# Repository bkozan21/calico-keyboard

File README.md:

# Calico Split Keyboard

This repository contains software and CAD files for a custom wireless split keyboard. I uses ZMK as firmware. The rest of this README is a tutorial about how to make this or a similar keyboard.

# Final product in action

[0001-1000.mp4](Split%20Keyboard/0001-1000.mp4)

# Table of contents

# Introduction

This was a personal project idea. I spent a lot of time during a week in front of a computer typing. Modern keyboards are not that ergonomic. As I was looking for a better keyboard, I came across custom keyboards and decided to make my own.

## Inspiration and Useful Sources

### Main Inspiration

These two videos from Ben Vallack and Christian Selig were my main inspiration. During the design and making of my own keyboard, I went back to these videos quite frequently. If you need more information about something, start with these videos.

[“The REAL Ergonomic Keyboard Endgame!” - How To Design & Make A Totally Custom Keyboard](https://www.youtube.com/watch?v=UKfeJrRIcxw)

[I Built My Dream Keyboard from Absolute Scratch](https://www.youtube.com/watch?v=7UXsD7nSfDY)

Here are the GitHub repositories for the keyboards from the videos above:

[ergogen/input/config-flipper.yaml at master · benvallack/ergogen](https://github.com/benvallack/ergogen/blob/master/input/config-flipper.yaml)

[caldera-keyboard/ergogen/config.yaml at main · christianselig/caldera-keyboard](https://github.com/christianselig/caldera-keyboard/blob/main/ergogen/config.yaml)

### Other useful sources and inspirations

https://www.frandieguez.com/posts/how-to-build-a-split-keyboard-lily58-pro/#putting-all-together

https://github.com/makgyber/kiai-split

https://www.ubiqueiot.com/posts/xiao-nrf52840-zmk

https://github.com/ubiqueIoT/GigaPad/tree/main

This is a very good and detailed tutorial for the ergogen software I used:

[Let's Design A Keyboard With Ergogen v4: Introduction](https://flatfootfox.com/ergogen-introduction/)

[Let's Design A Keyboard With Ergogen v4: Reversible Split Keyboard Tips](https://flatfootfox.com/ergogen-part6-reversible-split/)

# Ingredients

<aside>
ℹ️

You don’t have to buy the items from the links I added. You can use any supplier or store or an equivalent product as long as it is compatible.

</aside>

| Name | Link | Quantity | Notes |
| --- | --- | --- | --- |
| Kailh Low Profile Choc Switches | https://splitkb.com/products/kailh-low-profile-choc-switches?variant=32171144380493&_su_rec=K7XPEFOSKQJ6HuOqu8JvlqgQJot6nW1wtNrVSzVyanA3C1YqsAHD4RuTCrJwP6FZxHm1uhMl3X4t7QNzuMuESyQ1RrEEgi36AF2GOhwYCAo9edE3fmjca5diy_bAAWXqCz8KgsL9PHYvucSHRDPHljyZl6D8sljBpnwmTNCeQKEJPHhKLW_XfV4Vj7vQilxc3kevMZ2U6zh7X3NKLHTFHpHWZRXFbdY0bCzeEJDRBogsHo5YQ6zEQlgKb0bRMkyONT2hpbjF&_su_rec_id=4e69f0e8-41da-4f02-ba84-3d4b565eb13f-1793966067 | 108 | I used 10 brown switches. Those are the arrow keys on both sides. For the red, I used reds. I did this because I was curious of the feeling of the browns. You can mix and match like me or stick to one type. |
| Keycap set | https://splitkb.com/products/mbk-legend-40s-choc-low-profile-keycaps?variant=43111026753795 | 1 | It doesn’t come with enough keycaps for a 108 key keyboard. You need extra keycaps if you have lots of keys. |
| Blank keycaps | https://splitkb.com/products/blank-mbk-choc-low-profile-keycaps?variant=31811487039565 | 56 | It might be a good idea to buy a couple more than you need just in case. Also, in the link I pasted, there are multiple options. I got only “10 x 1u”. That is a pack with ten 1 unit keycaps. |
| Kailh Hotswap Sockets | https://splitkb.com/products/kailh-hotswap-sockets?variant=39472161456205 | 108 | Make sure that you get the “choc” version. They need to match the switches. |
| SMD Diodes | https://splitkb.com/products/smd-diodes?variant=42283984060675 | 108 |  |
| nice!nano Microcontroller board | https://splitkb.com/products/nice-nano?variant=39408154116173 | 2 |  |
| Mill Max Low Profile Sockets | https://splitkb.com/products/mill-max-low-profile-sockets?variant=31945995845709 | 2 | I didn’t like these sockets that much. It is nice that they place the MCU board low but the pins are very thin. It is easy to bend a pin. You can also use a normal male and female headers. |
| JST PH 2 pin Female Socket | https://www.digikey.nl/en/products/detail/jst-sales-america-inc/S2B-PH-K-S/926626 | 2 |  |
| Li-Po battery | https://www.tinytronics.nl/en/power/batteries/li-po/pkcell-li-po-battery-3.7v-150mah-jst-ph-lp402025https://www.tinytronics.nl/en/power/batteries/li-po/pkcell-li-po-battery-3.7v-150mah-jst-ph-lp402025 | 2 | You can use a different capacity one. |
| Small on/off switch | https://www.tinytronics.nl/en/switches/manual-switches/slide-switches/small-switch-for-pcb-or-breadboard | 2 |  |
| Small pushbutton | https://www.tinytronics.nl/en/switches/manual-switches/pcb-switches/tactile-pushbutton-switch-momentary-4pin-6*6*6mm | 2 |  |
| M3 spacer - 10 mm - female to female |  | 22 |  |
| M3 bolt - 10 mm | https://www.tinytronics.nl/en/tools-and-mounting/installation-and-mounting-material/bolts/m3-bolt-10mm-thread-100-pieces | 22 |  |
| M3 bolt - 5 mm | https://www.tinytronics.nl/en/tools-and-mounting/installation-and-mounting-material/bolts/m3-bolt-5mm-thread-100-bolts | 22 |  |
| Rubber feet | https://nl.bauhaus/vilt-meubeldoppen/fix-o-moll-antislip-en-geluiddempers-12-mm/p/20893129 | At least 8 | I used 4 per side but in the 3d models, I added places for more. |

<aside>
⚠️

Be very careful with the LiPo battery. Do not puncture or cut it. Do not short its cables. Otherwise, it might explode and/or cause a fire.

</aside>

<aside>
ℹ️

I call my keyboard “Calico”. (It comes from the cat fur pattern). I don’t exactly know why I chose this name. 

</aside>

<aside>
ℹ️

All the software, 3d files, and the PCB files are on a GitHub repository. You can just use those files if you are making the exact same keyboard or use them as inspiration.

[GitHub - bkozan21/calico-keyboard](https://github.com/bkozan21/calico-keyboard/)

</aside>

# Making the layout (Ergogen)

<aside>
ℹ️

My goal for using ergogen was to generate a PCB layout. If you want to design your own layout, keep reading this section. If you are replicating my design, you can just get the PCB from my GitHub repository and skip to the next section.

https://github.com/bkozan21/calico-keyboard

</aside>

I used a software called ergogen to create the layout of my keyboard. It is a software for creating custom keyboard layouts. It can generate dxf files that you can use for designing a case and more importantly it can automatically generate a KiCad pcb file with the footprints placed according to your design. Then all you have to do is to route the traces. The first link below is the online configurator. The second link is the documentation.

[Ergogen](https://ergogen.xyz/)

[Getting Started | Ergogen docs](https://docs.ergogen.xyz/)

 with my yaml file. On the right are all the output files defined by the yaml.](Split%20Keyboard/Screenshot_20261106_202545.png)

A screenshot of [ergogen.xyz](http://ergogen.xyz) with my yaml file. On the right are all the output files defined by the yaml.

Ergogen takes a yaml file as an input. Here you design where each switch goes. In addition, you can define the board shape, and configure the pcb. You can my final yaml file here: https://github.com/bkozan21/calico-keyboard/blob/main/ergogen_input/calico_ergogen_layout.yaml 

I didn’t start from scratch. Ergogen comes with a couple of examples. I started with the Absolem template. You can learn more about this design here: https://zealot.hu/absolem/. I wanted more keys so I added keys around. I also wanted to make a split keyboard so I deleted the right half. I designed only the left side because the right side is the exact same but mirrored. 

<aside>
✅

If you are designing your own keyboard, a good idea to download the demo.dxf file ergogen generates and print it on an A4. This way you can try your layout in real life. Put your hands on it and see if you like the switch positions.

</aside>

## Main sections in the ergogen yaml file

<aside>
✅

In the online configuratior, you can view the outputs as you are making changes. For example, click on the demo.dxf on the right and it will show you the dxf file. The dxf will change automatically as you are making changes.

</aside>

### Points

```yaml
points:
  zones:
    matrix:
      anchor:
        rotate: 5
        shift: [100, -150]
      columns:
        extra3:
          key.column_net: col1
        extra2:
           key.column_net: col2
...
```

This where the switch placements are made. They are defined as columns and rows. I have three sections. Matrix, thumbfan, and arrows. These are separately defined clusters. `key.column_net` and `row_net` are for assigning PCB nets.

### Outlines

Here, I defined a polygon by specifying points with respect to keys. I used this polygon as the board outline. Using 

### PCB

This is where I defined the footprints to be used in the PCB. You can configure some settings for each footprint. Ergogen supports footprints from the following GitHub repository: https://github.com/ceoloide/ergogen-footprints. For available configuration options look at the files in this repository. You can view the PCB as you are making changes in the online ergogen editor.

Live preview of the pcb file on ergogen.xyz.

Here, you need to think about your columns and rows and how they will connect to the microcontroller board. I have 54 keys per side. The microcontroller doesn’t have 54 pins. This is often the case. There are more keys than the microcontroller pins. That’s why a matrix is used. Columns and rows are actually important. Each key is part of a column and row. It is explained in great detail in the link below. It is best if you just read it instead of me trying to explain it. 

[Let's Design A Keyboard With Ergogen v4: The PCB (Part 3)](https://flatfootfox.com/ergogen-part3-pcbs/)

I used a 9 x 7 matrix. Yes, it is 9 time 7 is 63 and I could have done 6 x 9 which is the exact number of keys I have but I just found it easier to have 7 rows instead of 6. If you look at my layout, there are 9 clear columns. For the arrows and the thumb cluster, I decided to use 2 rows. I just found this easier for routing. 

<aside>
⚠️

The net names for the PCB are created from the row and column names defined under points in the yaml file. Make sure to use different row and column names for the clusters. Otherwise, you will can get switch pads with the same net name even though those pads are not supposed to be the same net (i.e connected).

For example, for the arrow cluster, I initially used “top” for a column and “right” for a “row”. This created a pad name “top_right”. In the main “matrix” cluster, I also had a switch with a “top_right” pad. Those are two different switches. Their pads must not be connected. That’s why I changed the rows and the columns of the arrow cluster to have a “arrows_” prefix such as “arrows_top” and “arrows_right”.

</aside>

For the footprints, make sure that you enable the reversible option. This way the same PCB can be used for both the left and the right side. For example, the hotswap sockets has pads on both sides. This way you can solder a socket to either side. The microcontroller board has these tiny pads next to the pin holes. You can put a solder bridge on those. This way you don’t have to put the microcontroller board upside down on one side. (This is just for esthetic reasons actually. An upside down microcontroller board would look ugly so people came up with this footprint option.)

The microconroller board footprint up close in the KiCad 3d viewer.

More info here:

[Let's Design A Keyboard With Ergogen v4: Reversible Split Keyboard Tips](https://flatfootfox.com/ergogen-part6-reversible-split/)

# The PCB

<aside>
ℹ️

Again, if you are just replicating my design, you can just use the PCB files in my GitHub repository. If you are designing your own keyboard or making modifications to my design, keep reading this section, otherwise you can skip this section.

https://github.com/bkozan21/calico-keyboard

</aside>

## Finalizing the Design

### Download the PCB file

Once you are done with your layout and you added all the footprints for the PCB in the ergogen yaml file, you can download the PCB from the ergogen online editor. After downloading, I wanted to edit the PCB file because I wanted to add some extra footprints that are not available in ergogen. That’s why I created a new kicad project first and then imported the ergogen generated PCB. I used the “File → Append Board” option. Then I added some extra footprints using “Place → Place Footprints”

### Add missing components

I added a regular three pin header (`PinHeader_1x03_P2.54mm_Vertical`) because that was the footprint of the on/off switch I used. Then I added a classic push (`SW_PUSH_6mm`)button for the microcontroller board reset. I noticed that using the schematic is not necessary. You can just click on a pad (sometimes you may need to click multiple times, otherwise you select the whole component) and change the net assignment in the properties panel. You can select from an existing net or create a new net.

Editing the net assignment of a pad in KiCad.

<aside>
⚠️

I had to change the pad assignment for the battery connector because it was the opposite of the battery I used. Check you batter connector and see which side is the positive and which side is the negative side. Update the footprint if necessary. Keep in mind which side you are going to place the JST battery connector. In my design, the JST batter connector goes to the bottom (same side as the hotswap sockets and the diodes)

</aside>

<aside>
⚠️

I also added another footprint. It has a circle in the silkscreen layer and 8 pins. This is for a joystick I planned to add. It is for mouse input. I didn’t have time to implement this feature so you can ignore this component.

</aside>

After placing the components, you can also add some logos or text in the silkscreen layers.

### Routing

If the previous steps are completed correctly, every pad must now have a net name. Now you need to route traces and connect the each pad where it needs to be connected. Don’t forget, there are two copper layers. You can switch between layers with vias. I used the default trace width of 0.25 mm and the default vias with diameter of 0.8 mm and a hole of 0.4 mm.

### Design Rule Check (DRC)

I planned to order the PCBs from JLCPCB. That’s why I wanted to add design rules so that I can check if my design is within their manufacturing capabilities. That’s why I added custom design rules that were created specifically according to the JLCPCB capabilities. I got these rules from a GitHub repository: https://github.com/Cimos/kicad-druid/blob/main/JLCPCB/JLCPCB-2L-1oz.kicad_dru You can add these rules in KiCad PCB view. Go to “File → Board Setup → Custom Rules” and copy and paste the contents of the file with the design rules.

Now, you can run the DRC with the custom rules. Go to “Inspect → Design Rules Checker” and click on the “Run DRC” button. I got errors for the pads of the JST1 battery connector. I ignored those. The PCB turned out fine. I also ignored the warnings. 

I ignored the errors on the JST1 footprint.

## Ordering the PCB

### Generate Gerber Files

These files are needed by the manufacturer. Again, you can find the ones I used in my GitHub repository. To generate: 

1. Go to “File → Plot”.
2. Select an output directory.
3. Click on “Generate Drill Files”
4. Click on “Generate” on the new window and then click “close”
5. Click on “Plot” and then close.
6. Now compress the output directory into a zip file. This is the file you need to upload to JLCPCB.

### Order from a manufacturer

I used JLCPCB. You need to upload the gerber file and select some options. Here are all the options I selected:

```
Gerber file: output2_Y2

Build Time: 24 hours

Base Material: FR-4

Layers: 2

Dimension: 218.7 mm* 151.6 mm 218.71mm* 151.6mm

PCB Qty: 5

Product Type: Industrial/Consumer electronics

Different Design: 1

Delivery Format: Single PCB

PCB Thickness: 1.6mm

Specify Stackup: no

PCB Color: Green

Silkscreen: White

Material Type: TG135

Via Covering: Tented

Surface Finish: LeadFree HASL

Deburring/Edge rounding: No

Outer Copper Weight: 1 oz

Gold Fingers: No

Electrical Test: Flying Probe Fully Test

Castellated Holes: no

Edge Plating: No

Mark on PCB: Remove Mark

Blind Slot: No

Min via hole size/diameter: 0.3mm/(0.4/0.45mm)

Via Plating Method: Not Specified

4-Wire Kelvin Test: No

Paper between PCBs: No

Appearance Quality: IPC Class 2 Standard

Confirm Production file: No

Silkscreen Technology: Ink-jet Printing Silkscreen

Package Box: With JLCPCB logo

Inspection Report: No

Board Outline Tolerance: ±0.2mm(Regular)

Impedance Test Report: No

UL Marking: No

Countersink Hole: No

Humidity Indicator Card: No

Shortage Preference: Require Full Quantity

Weight: 0.7kg
```

I used “DHL Express (DDP)” as my shipping option. This shipping option handles the customs duties and taxes. I paid around 6 euros for 24-hour manufacturing. I ordered the PCBs on Saturday evening, and I picked the package up on Friday evening from a DHL point.

## Soldering

There is nothing unique about soldering the parts. Follow general advice. Make sure to apply flux. I will still give some tips and points to take into account.

<aside>
⚠️

Don’t forget to flip the PCB when doing the other side.

</aside>

Left side bottom

Both sides bottom

A hotswap socket and a diode up close

### Hotswap Sockets

The way I soldered hotswap sockets is as follows. I put the socket on the pads. Made sure that it is flush with the PCB and flat. I soldered one leg onto its pad. I didn’t immediately took the soldering iron away. After putting solder, I kept the iron on the pad to keep the solder still melted. Then I pushed on the socket with a pair of tweezers to make sure that it was flat and fully up against the PCB. Then while pushing with the tweezers, I pulled the soldering iron away. After a second or two, I stopped pushing with the tweezers. I did this because when soldering the first leg, the socket might lift up. The push with the tweezers makes sure that the socket is flat at the end of the soldering process. After soldering the first leg, I soldered the second leg as usual. 

A soldered socket

A soldered socket from the front

### Diodes

Diodes have direction. It matters which way you solder them! They are marked with a line on one side. The diode pads are marked with a silkscreen. Make sure the lines match! The text and the line on a diode can be difficult to see. Try looking at the diode from different angles. In certain angles, the markings are easy to read and from other angles, they are difficult to read.

Here, a diode is placed next to its pads. It is not soldered! It is not very clear, but towards the right side, you can see a line. The diode symbol on the silkscreen also has a line towards the right.

A properly soldered diode. Here, you can see the line on the right more clearly.

The way I soldered the diodes is as follows:

1. Place some solder (with the soldering iron) on one of the pads on the PCB.
2. Hold the diode with a pair of tweezers in one hand.
3. Hold the soldering iron with your other hand.
4. Heat the solder on the PCB,
5. Push one leg of the diode into the melted solder.
6. Remove the soldering iron while holding the diode in place.
7. Solder the other leg of the diode normally.

These SMD diodes are tiny. Use a pair of tweezers with very thin tips.

### The microcontroller board

First, solder the female sockets. Then put the microcontroller on top of the sockets and insert the pins through the microcontroller board into the sockets. Be very careful and gentle. The pins can bend easily. Once the pins are pushed down fully, you can solder them to the microcontroller board. 

Then, you need to put solder bridges to the pads on the other side of the PCB. 

I put some hot glue on top of the battery terminals just to have some extra protection against shorts.

Solder the rest of the components similarly.

# The Case

<aside>
ℹ️

The STLs are also on my GitHub repository.

https://github.com/bkozan21/calico-keyboard

</aside>

I designed the case in Onshape. I made the document public. You can view it here:

[Onshape](https://cad.onshape.com/documents/db90108e0c18a49f77f814f0/w/d8d8382bf78da29ebfbabf1b/e/875cb3c507a1a049483ec79f?renderMode=0&uiState=6aee2f85786fe483e2490886)

You need to 3d print the case parts. The case for one side consists of one top layer, one bottom layer, and 11 spacers. The 3d files are designed for the left side. For the right side, you can mirror the top and bottom layers in the slicer. The spacers are discs. They don’t need to be mirrored.

Recommended print orientation for the top layer.

Recommended print orientation for the bottom layer.

I used 100% infill for the top layer and the spacers. I used 15% infill for the bottom layer. I used normal PLA for everything. I used the original Prusa i3 MKS3S+ printers with a 0.8 nozzle in the TU Delft Science Centre. I printed everything with 0.40 mm layer height. The top layer requires a little bit of support around the microcontroller. I used tree supports in the Prusa slicer. They came of relatively easily.

<aside>
⚠️

Depending on the printer you use, you might need to adjust the tolerances in the 3d models.

</aside>

<aside>
⚠️

I added a small inset in the bottom plate for the battery, but I ended up not using it. After removing supports, it was still rough. Just connecting the battery to the socket was enough for me.

</aside>

# Assembly

<aside>
⚠️

Be very careful with the LiPo battery. Do not puncture or cut it. Do not short its cables. Otherwise, it might explode and/or cause a fire.

</aside>

1. Make sure the power switch is in the off position and plug in the battery.
2. Put the PCB into the top layer. The microcontroller must face up.

1. Put a 10 mm M3 bolt through the mounting holes and the PCB. Then put a 3d printer spacer and a 10 mm M3 spacer.

The black piece under the brass M3 spacer is a 3d printer spacer.

1. Put the bottom layer 3d print and attach it with 5 mm M3 bolts.

1. Stick the rubber feet to their insets.

1. Attach keycaps to the switches. (I did this first because I noticed that keycaps require a lot of force to attach. When you place the switches first, you apply the force to the PCB when attaching a keycap. I didn’t want to apply a lot of force to the PCB,
2. Put switches into the sockets.

# Configuring the software

<aside>
ℹ️

If you are replicating my design, go to the downloading the firmware section.

</aside>

<aside>
ℹ️

Please refer to my GitHub repository. I didn’t put everything here to make this tutorial easier to follow.

https://github.com/bkozan21/calico-keyboard

</aside>

For the software, I used ZMK. It is an open-source keyboard software that supports wireless split keyboards.

[Hello from ZMK Firmware | ZMK Firmware](https://zmk.dev/)

<aside>
ℹ️

I performed these operations on a computer running Ubuntu 24.04.5 LTS. If you are trying this on Windows and run into issues, you can try using the Windows Subsystem for Linux. 

</aside>

1. Create a GitHub account if you don’t have one. https://github.com/
2. Download the ZMK CLI. For that, follow the steps here, from start until **`Config Repo Setup`**
    
    [Installing ZMK | ZMK Firmware](https://zmk.dev/docs/user-setup?operating-system=linux#prerequisites)
    
    When you are done, run `zmk --version` on your terminal. If everything went well, this command should print a version number such as `0.5.0`.
    
3. Now, it is time to create a repository for the firmware files for the macro pad. Change directory to a place where you would like to store the firmware files. There will be a new folder created here automatically.
    
    ```bash
    cd ~/Documents
    ```
    
4. Now run `zmk init` 
    
    You will see two options. You can use up and down arrows to select an option. Select `Create a new ZMK config repo` and hit enter.
    
5. It will display a text about creating a repository. Here, once you hit enter, it will open a webpage to create a GitHub repository.

Here, you can change the repository name. If you want, you can set the visibility to private. Then scroll down and click `Create Repository`.

1. Now, you need to copy the repository URL and past it to the terminal. You will find the repository URL when you click on the green `Code` button. Depending on how you authenticated with the GitHub CLI, use either the HTTPS URL or the SSH URL. (You can try both. If one doesn’t work, try the other one)

Hit enter. You can then enter a folder name if you want or leave it default by hitting enter again. At the end, a folder with ZMK project files will be created. If it says “Would you like to add a keyboard now?” Enter `n` and hit enter. We will not add a keyboard, we will create a new one.

1. Change directory to the newly created folder and run `zmk keyboard new`. 
    1. Enter the name of the keyboard, then pick an abbreviated name, then an ID. Try to make these similar to each other. 
    2. Select `shield` as the keyboard type. 
    3. Select `pro_micro` as the interconnect. (The nice_nano microcontroller we use has the same pin layout as a pro_micro)
    4. Select `split` as the keyboard layout.
2. Open the folder in Visual Studio Code. (You can use any text editor, but I find VS Code nice)
3. Add these lines to `build.yaml`:
    
    ```yaml
    include:  
      - board: nice_nano_v2    
        shield: calico_left
      - board: nice_nano_v2    
        shield: calico_right
    ```
    
    I named my keyboard “calico”. That’s why I wrote “calico_left” and “calico_right”. You an use the name of your keyboard.
    
4. Now, go to `/boards/shilds/<name of your keyboard>/` 

<aside>
ℹ️

I left some files as they are. I modified some files. If you are using a different microcontroller or doing something different than I did, you may need to configure your software files differently. In addition, if you want some different behaviour, you might need to change these configuration files. Refer to the ZMK docs. Below is the page about adding a new keyboard to ZMK.

[New Keyboard Shield | ZMK Firmware](https://zmk.dev/docs/hardware-integration/new-shield)

</aside>

1. Leave `Kconfig.defconfig` as it is.
2. Leave `Kconfig.shield` as it is.
3. Edit `<name of your keyboard>-layouts.dtsi` 
    1. Add  row-gpios. Note: Here, you need to use pro micro pin numbers. Refer to the image below. They need to be set as `(GPIO_ACTIVE_HIGH | GPIO_PULL_DOWN)`
    2. Define a default transform. Here, the number of columns needs to be defined as twice as many as the actual columns on one side. You configure ZMK as if your keyboard is one piece instead of two separate pieces.
    3. Define a map. Here you define where each switch is (i.e which row and column). My matrix doesn’t have switches in certain locations. I skipped those switches. That’s why there are gaps in my map.
4. Edit `<name of your your keyboard>_left.overlay` and `<name of your your keyboard>_right.overlay` :
    1. Add col-gpios here. Note: The order of the col-gpios for the right side must be the opposite of the left side.
    2. Define a coll offset for the right side. This must be the number of columns you have on one side. Here, we are basically telling ZMK to look at the right half of the keymap.
5. Add the following lines to `<name of your keyboard>.conf` :

```
CONFIG_ZMK_SLEEP=y
CONFIG_BT_CTLR_TX_PWR_PLUS_8=y
CONFIG_ZMK_KEYBOARD_NAME="calico-keyboard"
CONFIG_ZMK_HID_CONSUMER_REPORT_USAGES_BASIC=y
```

1. Configure the keymap by changing `<name of your keyboard>.keymap`
    
    <aside>
    ℹ️
    
    Refer to ZMK documentation for details:
    
    https://zmk.dev/docs/keymaps
    
    https://zmk.dev/docs/keymaps/list-of-keycodes
    
    </aside>
    
2. Edit `<name of your keyboard>.zmk.yml`:
    1. Remove the studio option from features because we are not going to use it.
3. After you are done with changing the files, commit and push your changes.
    
    <aside>
    ℹ️
    
    You don’t need to know how to use git to follow this tutorial but it might be nice to be familiar with it to understand what is going on. Here you can read about git: https://www.geeksforgeeks.org/git/git-tutorial/
    
    </aside>
    
    You can use the built-in VS Code version control tools to commit and push or you can use the command line
    
    1. Stage all your changes. With this command, you mark all your changes as ready to be committed.
        
        ```bash
        git add .
        ```
        
    2. Commit your changes. With this command, you record your changes. The text in quotes is the commit message. This is a short note that describes what the commit achieves. You can write whatever makes sense to you.
        
        ```bash
        git commit -m "initial board files"
        ```
        
    3. Push your changes. With this command, all your local commits are sent to the server. In this case, it is GitHub.

# Download the firmware

<aside>
ℹ️

If you are replicating my design, just go to the release v1.0.0 and download the `firmware.zip` file. You can find the link to that release here:

[Release v1.0.0 · bkozan21/calico-keyboard](https://github.com/bkozan21/calico-keyboard/releases/tag/v1.0.0)

If you made your own design, keep reading.

</aside>

When you push, a GitHub action is triggered that will build the firmware. This is set up through the ZMK template that the repository is based on. Click on `Actions` in the repository. It shows all the triggered actions.

<aside>
ℹ️

 If an action fails, it shows up as a red cross. You can enter and see the output text. Based on the error messages in the output, you can fix the issue locally, commit, and push. A new action will be triggered.

For example, in a different project repository, I made a typo in the build.yaml. Here, you can see that it says `No board named 'seeduino_xiao_ble'` . It should have been `seeeduino_xiao_ble` with one more ‘e’.

</aside>

Go to the latest action. Make sure that it was successful. It should appear with a green tick. Scroll down to the Artifacts section. There is the firmware. Download it and unzip it.

There should be two .uf2 files in the unzipped folder. One firmware file for each side.

# Flash the firmware

1. Connect the left side’s microcontroller (nice_nano) board to your computer with a USB-C cable. 
2. Double-click the reset button (It is on the PCB).  The microcontroller will show up on your laptop as a USB flash drive.
3. Copy the .uf2 file for the left side and paste it to the flash drive that appeared. When the transfer is complete, you might get an error. This is fine. I think the microcontroller board automatically disconnects. 
4. Repeat all the steps above for the right side.

# Connecting to a device

Set the switch to the on position on both sides. Now, you should be able to find the keyboard as a Bluetooth device and connect to it. It shows up with the name you set during the initial setup. You will only see one Bluetooth device. The right side communicates with the left side. The left side communicates with your Bluetooth device.

Once it is connected, it works like a normal Bluetooth keyboard. Once you have it paired with a computer, every time you turn on the keyboard, it will automatically connect to that computer.

<aside>
✅

Congrats. If you reached this point, this means you have your own custom wireless split keyboard.

</aside>

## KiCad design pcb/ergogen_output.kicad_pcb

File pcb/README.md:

# PCB
This directory contains KiCad files for the Calico keyboard. The file names are called ergogen_output because the layout was generated using ergogen. However, the pcb design contains some updates. Of course, I added traces. In addition, I added some extra footprints and some silkscreen text.

## Custom Design Rules
I used custom design rules made specifically for JLCPCB. I got those custom design rules from https://github.com/Cimos/kicad-druid/tree/main.

The file I used: https://github.com/Cimos/kicad-druid/blob/main/JLCPCB/JLCPCB-2L-1oz.kicad_dru

## Gerber files
The gerber files I used to order the PCB can be found in the gerber_files directory.

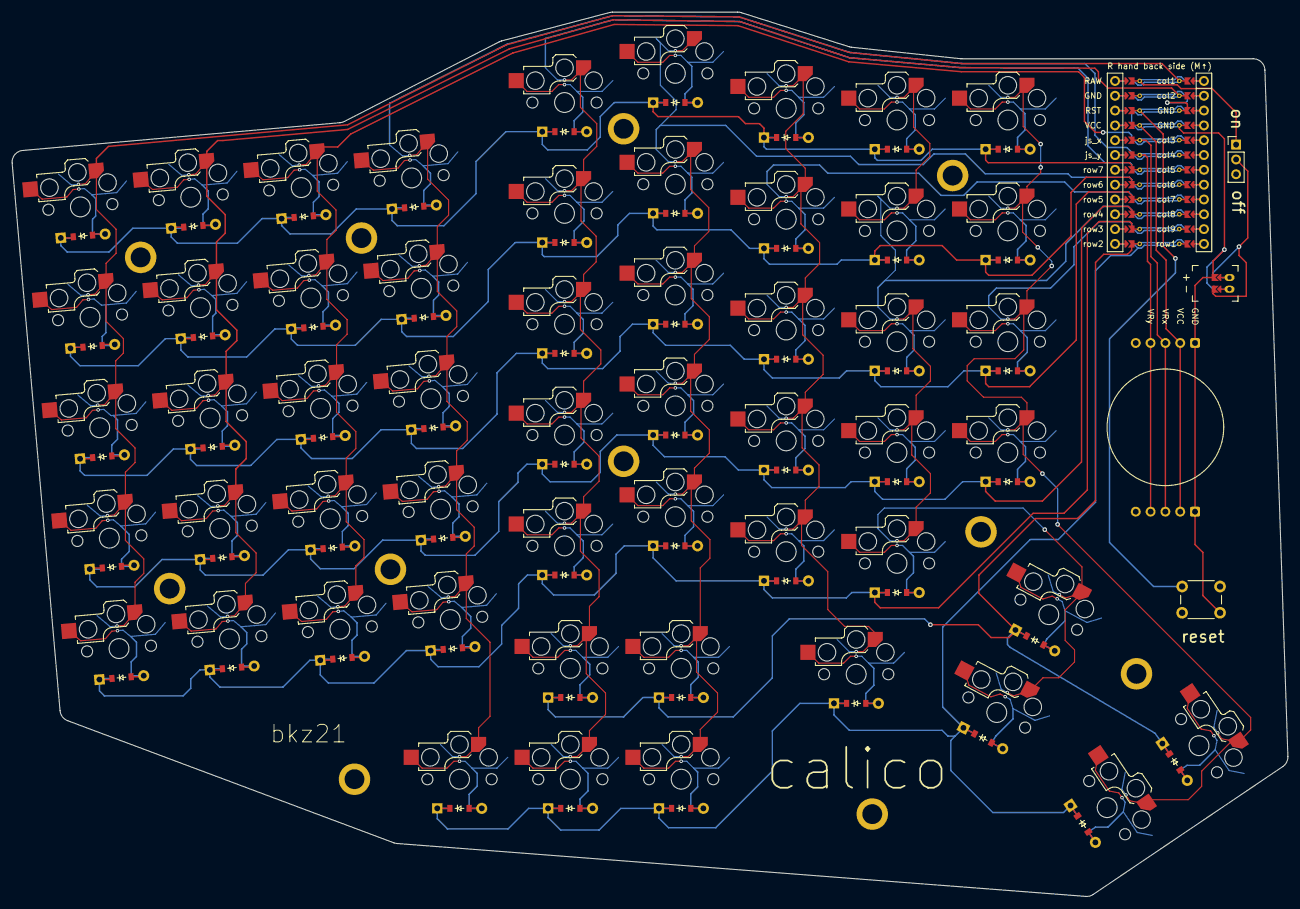
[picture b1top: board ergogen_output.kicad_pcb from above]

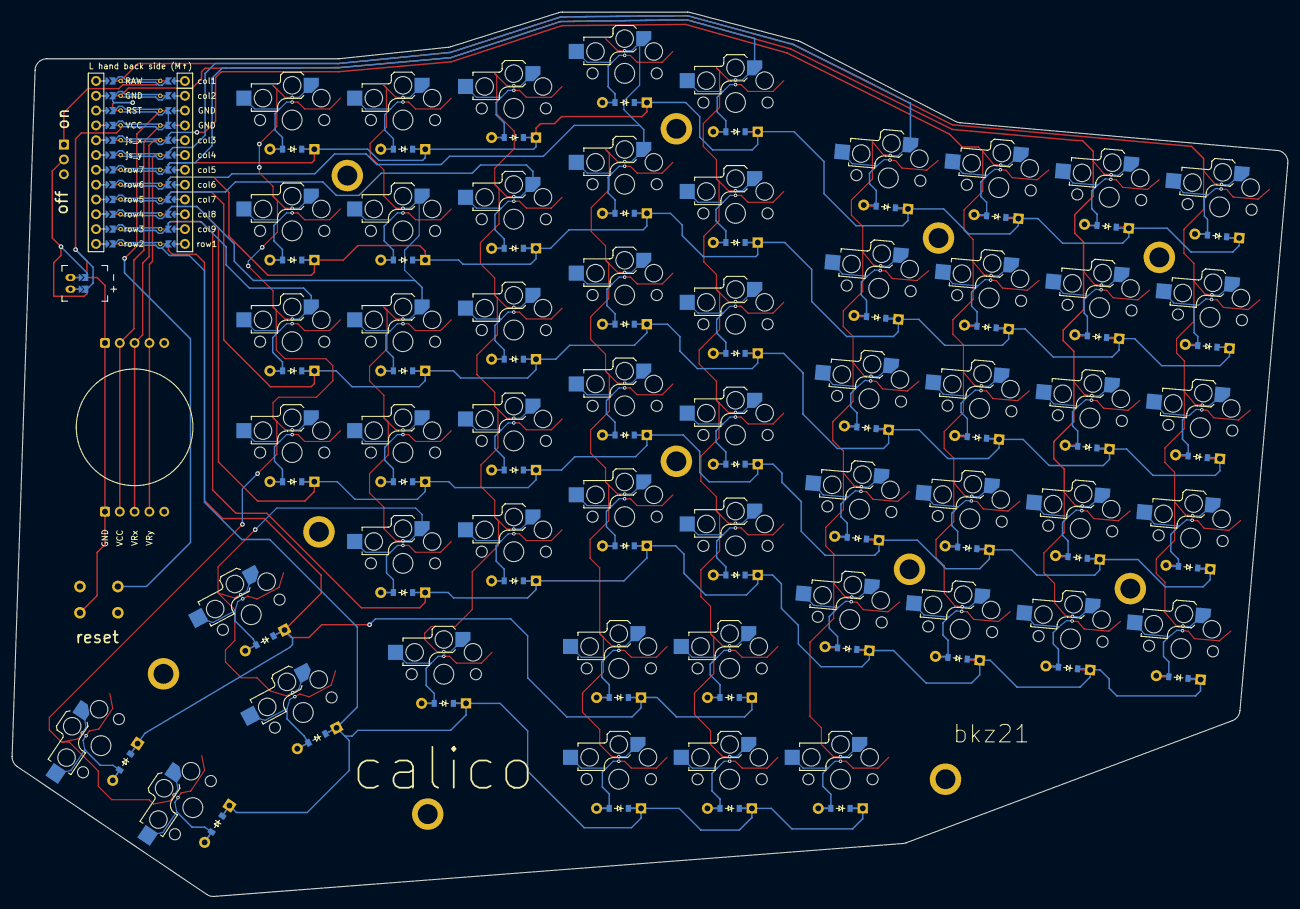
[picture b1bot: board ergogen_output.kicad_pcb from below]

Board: 2 copper layers, 218.7 x 151.6 mm, 121 parts (54 on the bottom side), 73 nets.

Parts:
D1, D2, D3, D4, D5, D6, D7, D8, D9, D10, D11, D12, D13, D14, D15, D16, D17, D18, D19, D20, D21, D22, D23, D24, D25, D26, D27, D28, D29, D30, D31, D32, D33, D34, D35, D36, D37, D38, D39, D40, D41, D42, D43, D44, D45, D46, D47, D48, D49, D50, D51, D52, D53, D54: diode_tht_sod123
H1, H2, H3, H4, H5, H6, H7, H8, H9, H10, H11: mounting_hole_plated
JST1: battery_connector_jst_ph_2
MCU1: mcu_nice_nano
S1, S2, S3, S4, S5, S6, S7, S8, S9, S10, S11, S12, S13, S14, S15, S16, S17, S18, S19, S20, S21, S22, S23, S24, S25, S26, S27, S28, S29, S30, S31, S32, S33, S34, S35, S36, S37, S38, S39, S40, S41, S42, S43, S44, S45, S46, S47, S48, S49, S50, S51, S52, S53, S54: switch_choc_v1_v2

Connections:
GND: JST1.1, MCU1.103, MCU1.104, MCU1.123
JST1_1: JST1.11, JST1.21, JST1.31
JST1_2: JST1.12, JST1.22, JST1.32
arrows_left_arrows_bottom: D50.2, S50.2
arrows_middle_arrows_bottom: D51.2, S51.2
arrows_middle_arrows_top: D52.2, S52.2
arrows_right_arrows_bottom: D53.2, S53.2
arrows_right_arrows_top: D54.2, S54.2
col1: MCU1.101, S1.1, S2.1, S3.1, S4.1, S5.1
col2: MCU1.102, S6.1, S7.1, S8.1, S9.1, S10.1
col3: MCU1.105, S11.1, S12.1, S13.1, S14.1, S15.1
col4: MCU1.106, S16.1, S17.1, S18.1, S19.1, S20.1, S50.1
col5: MCU1.107, S21.1, S22.1, S23.1, S24.1, S25.1, S51.1, S52.1
col6: MCU1.108, S26.1, S27.1, S28.1, S29.1, S30.1, S53.1, S54.1
col7: MCU1.109, S31.1, S32.1, S33.1, S34.1, S35.1, S45.1
col8: MCU1.110, S36.1, S37.1, S38.1, S39.1, S40.1, S46.1, S47.1
col9: MCU1.111, S41.1, S42.1, S43.1, S44.1, S48.1, S49.1
extra1_bottom: D11.2, S11.2
extra1_functions: D15.2, S15.2
extra1_home: D12.2, S12.2
extra1_numbers: D14.2, S14.2
extra1_top: D13.2, S13.2
extra2_bottom: D6.2, S6.2
extra2_functions: D10.2, S10.2
extra2_home: D7.2, S7.2
extra2_numbers: D9.2, S9.2
extra2_top: D8.2, S8.2
extra3_bottom: D1.2, S1.2
extra3_functions: D5.2, S5.2
extra3_home: D2.2, S2.2
extra3_numbers: D4.2, S4.2
extra3_top: D3.2, S3.2
far_thumb: D48.2, S48.2
far_thumb_up: D49.2, S49.2
home_thumb: D46.2, S46.2
home_thumb_up: D47.2, S47.2
index_bottom: D31.2, S31.2
index_functions: D35.2, S35.2
index_home: D32.2, S32.2
index_numbers: D34.2, S34.2
index_top: D33.2, S33.2
inner1_bottom: D36.2, S36.2
inner1_functions: D40.2, S40.2
inner1_home: D37.2, S37.2
inner1_numbers: D39.2, S39.2
inner1_top: D38.2, S38.2
inner2_functions: D44.2, S44.2
inner2_home: D41.2, S41.2
inner2_numbers: D43.2, S43.2
inner2_top: D42.2, S42.2
middle_bottom: D26.2, S26.2
middle_functions: D30.2, S30.2
middle_home: D27.2, S27.2
middle_numbers: D29.2, S29.2
middle_top: D28.2, S28.2
near_thumb: D45.2, S45.2
pinky_bottom: D16.2, S16.2
pinky_functions: D20.2, S20.2
pinky_home: D17.2, S17.2
pinky_numbers: D19.2, S19.2
pinky_top: D18.2, S18.2
ring_bottom: D21.2, S21.2
ring_functions: D25.2, S25.2
ring_home: D22.2, S22.2
ring_numbers: D24.2, S24.2
ring_top: D23.2, S23.2
row1: D45.1, D46.1, D48.1, D50.1, D51.1, D53.1, MCU1.112
row2: D47.1, D49.1, D52.1, D54.1, MCU1.113
row3: D1.1, D6.1, D11.1, D16.1, D21.1, D26.1, D31.1, D36.1, MCU1.114
row4: D2.1, D7.1, D12.1, D17.1, D22.1, D27.1, D32.1, D37.1, D41.1, MCU1.115
row5: D3.1, D8.1, D13.1, D18.1, D23.1, D28.1, D33.1, D38.1, D42.1, MCU1.116
row6: D4.1, D9.1, D14.1, D19.1, D24.1, D29.1, D34.1, D39.1, D43.1, MCU1.117
row7: D5.1, D10.1, D15.1, D20.1, D25.1, D30.1, D35.1, D40.1, D44.1, MCU1.118
